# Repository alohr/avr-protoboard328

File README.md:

avr-protoboard328
=================

A prototyping board for the AVR atmega328p. 

## Images

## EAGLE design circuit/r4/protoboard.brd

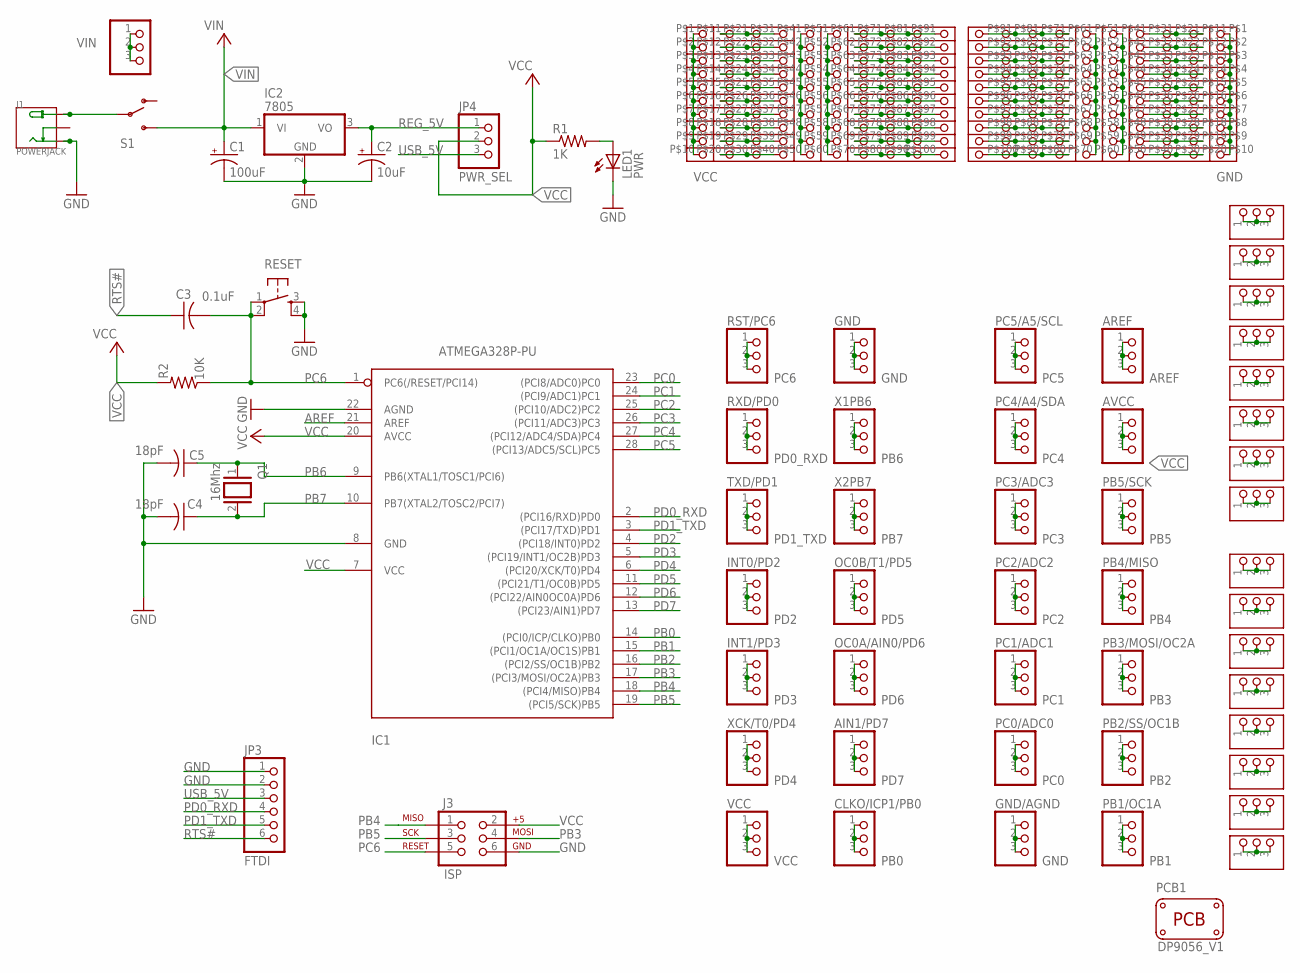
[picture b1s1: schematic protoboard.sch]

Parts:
AIN1/PD7: PINHD-1X3; 1X03
AREF: PINHD-1X3; 1X03
AVCC: PINHD-1X3; 1X03
C1: 100uF; CPOL-RADIAL-100UF-25V
C2: 10uF; CPOL-RADIAL-10UF-25V
C3: 0.1uF; C025-025X050
C4, C5: 18pF; C025-025X050
CLKO/ICP1/PB0: PINHD-1X3; 1X03
GND: PINHD-1X3; 1X03
GND/AGND: PINHD-1X3; 1X03
IC1: ATMEGA328P-PU; DIL28-3
IC2: 7805; TO220H
INT0/PD2, INT1/PD3: PINHD-1X3; 1X03
J1: POWERJACK; PW-3P-2.1
J3: ISP; 2X3
JP3: FTDI; 1X06
JP4: PWR_SEL; 1X03
LED1: PWR; LED3MM
OC0A/AIN0/PD6, OC0B/T1/PD5: PINHD-1X3; 1X03
PB1/OC1A, PB2/SS/OC1B, PB3/MOSI/OC2A, PB4/MISO, PB5/SCK: PINHD-1X3; 1X03
PC0/ADC0, PC1/ADC1, PC2/ADC2, PC3/ADC3, PC4/A4/SDA, PC5/A5/SCL: PINHD-1X3; 1X03
PCB1: PCB_DP_RECTANGLE-56X90; DP9056_V1
Q1: 16Mhz; QS
R1: 1K; 0207/7
R2: 10K; 0207/7
RESET: TAC_SWITCHPTH; TACTILE-PTH
RST/PC6: PINHD-1X3; 1X03
RXD/PD0: PINHD-1X3; 1X03
S1: SWITCH-SPDTPTH; SWITCH-SPDT
TXD/PD1: PINHD-1X3; 1X03
U$1, U$3: PROTOFIELD-10X10
U$4, U$5, U$6, U$7, U$8, U$9, U$10, U$11, U$12, U$13, U$14, U$15, U$16, U$17, U$18, U$19: PROTOFIELD-3
VCC: PINHD-1X3; 1X03
VIN: +9V; 1X03
X1PB6, X2PB7: PINHD-1X3; 1X03
XCK/T0/PD4: PINHD-1X3; 1X03

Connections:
AREF: AREF.1, AREF.2, AREF.3, IC1.21 (AREF)
GND: C1.2 (-), C2.2 (-), C4.2, C5.2, GND.1, GND.2, GND.3, GND/AGND.1, GND/AGND.2, GND/AGND.3, IC1.8 (GND), IC1.22 (AGND), IC2.2 (GND), J1.-1 (-), J3.6, JP3.1, JP3.2, LED1.K (C), RESET.3, RESET.4, U$3.P$1 (1), U$3.P$2 (5), U$3.P$3, U$3.P$4, U$3.P$5, U$3.P$6, U$3.P$7, U$3.P$8, U$3.P$9, U$3.P$10
unnamed: J1.+, S1.2
unnamed: LED1.A, R1.2
unnamed: U$4.1, U$4.2, U$4.3
unnamed: U$5.1, U$5.2, U$5.3
unnamed: U$6.1, U$6.2, U$6.3
unnamed: U$7.1, U$7.2, U$7.3
unnamed: U$8.1, U$8.2, U$8.3
unnamed: U$9.1, U$9.2, U$9.3
unnamed: U$10.1, U$10.2, U$10.3
unnamed: U$11.1, U$11.2, U$11.3
unnamed: U$12.1, U$12.2, U$12.3
unnamed: U$13.1, U$13.2, U$13.3
unnamed: U$14.1, U$14.2, U$14.3
unnamed: U$15.1, U$15.2, U$15.3
unnamed: U$16.1, U$16.2, U$16.3
unnamed: U$17.1, U$17.2, U$17.3
unnamed: U$18.1, U$18.2, U$18.3
unnamed: U$19.1, U$19.2, U$19.3
unnamed: U$1.P$41, U$1.P$42, U$1.P$43, U$1.P$44, U$1.P$45, U$1.P$46, U$1.P$47, U$1.P$48, U$1.P$49, U$1.P$50
unnamed: U$1.P$51, U$1.P$52, U$1.P$53, U$1.P$54, U$1.P$55, U$1.P$56, U$1.P$57, U$1.P$58, U$1.P$59, U$1.P$60
unnamed: U$1.P$61, U$1.P$71, U$1.P$81, U$1.P$91
unnamed: U$1.P$62, U$1.P$72, U$1.P$82, U$1.P$92
unnamed: U$1.P$63, U$1.P$73, U$1.P$83, U$1.P$93
unnamed: U$1.P$64, U$1.P$74, U$1.P$84, U$1.P$94
unnamed: U$1.P$65, U$1.P$75, U$1.P$85, U$1.P$95
unnamed: U$1.P$66, U$1.P$76, U$1.P$86, U$1.P$96
unnamed: U$1.P$67, U$1.P$77, U$1.P$87, U$1.P$97
unnamed: U$1.P$68, U$1.P$78, U$1.P$88, U$1.P$98
unnamed: U$1.P$69, U$1.P$79, U$1.P$89, U$1.P$99
unnamed: U$1.P$70, U$1.P$80, U$1.P$90, U$1.P$100
unnamed: U$1.P$11 (2), U$1.P$21 (3), U$1.P$31 (4)
unnamed: U$1.P$12 (6), U$1.P$22 (7), U$1.P$32 (8)
unnamed: U$1.P$13, U$1.P$23, U$1.P$33
unnamed: U$1.P$14, U$1.P$24, U$1.P$34
unnamed: U$1.P$15, U$1.P$25, U$1.P$35
unnamed: U$1.P$16, U$1.P$26, U$1.P$36
unnamed: U$1.P$17, U$1.P$27, U$1.P$37
unnamed: U$1.P$18, U$1.P$28, U$1.P$38
unnamed: U$1.P$19, U$1.P$29, U$1.P$39
unnamed: U$1.P$20, U$1.P$30, U$1.P$40
unnamed: U$3.P$61, U$3.P$71, U$3.P$81, U$3.P$91
unnamed: U$3.P$62, U$3.P$72, U$3.P$82, U$3.P$92
unnamed: U$3.P$63, U$3.P$73, U$3.P$83, U$3.P$93
unnamed: U$3.P$64, U$3.P$74, U$3.P$84, U$3.P$94
unnamed: U$3.P$65, U$3.P$75, U$3.P$85, U$3.P$95
unnamed: U$3.P$66, U$3.P$76, U$3.P$86, U$3.P$96
unnamed: U$3.P$67, U$3.P$77, U$3.P$87, U$3.P$97
unnamed: U$3.P$68, U$3.P$78, U$3.P$88, U$3.P$98
unnamed: U$3.P$69, U$3.P$79, U$3.P$89, U$3.P$99
unnamed: U$3.P$70, U$3.P$80, U$3.P$90, U$3.P$100
unnamed: U$3.P$51, U$3.P$52, U$3.P$53, U$3.P$54, U$3.P$55, U$3.P$56, U$3.P$57, U$3.P$58, U$3.P$59, U$3.P$60
unnamed: U$3.P$41, U$3.P$42, U$3.P$43, U$3.P$44, U$3.P$45, U$3.P$46, U$3.P$47, U$3.P$48, U$3.P$49, U$3.P$50
unnamed: U$3.P$11 (2), U$3.P$21 (3), U$3.P$31 (4)
unnamed: U$3.P$12 (6), U$3.P$22 (7), U$3.P$32 (8)
unnamed: U$3.P$13, U$3.P$23, U$3.P$33
unnamed: U$3.P$14, U$3.P$24, U$3.P$34
unnamed: U$3.P$15, U$3.P$25, U$3.P$35
unnamed: U$3.P$16, U$3.P$26, U$3.P$36
unnamed: U$3.P$17, U$3.P$27, U$3.P$37
unnamed: U$3.P$18, U$3.P$28, U$3.P$38
unnamed: U$3.P$19, U$3.P$29, U$3.P$39
unnamed: U$3.P$20, U$3.P$30, U$3.P$40
PB0: CLKO/ICP1/PB0.1, CLKO/ICP1/PB0.2, CLKO/ICP1/PB0.3, IC1.14 ((PCI0/ICP/CLKO)PB0)
PB1: IC1.15 ((PCI1/OC1A/OC1S)PB1), PB1/OC1A.1, PB1/OC1A.2, PB1/OC1A.3
PB2: IC1.16 ((PCI2/SS/OC1B)PB2), PB2/SS/OC1B.1, PB2/SS/OC1B.2, PB2/SS/OC1B.3
PB3: IC1.17 ((PCI3/MOSI/OC2A)PB3), J3.4, PB3/MOSI/OC2A.1, PB3/MOSI/OC2A.2, PB3/MOSI/OC2A.3
PB4: IC1.18 ((PCI4/MISO)PB4), J3.1, PB4/MISO.1, PB4/MISO.2, PB4/MISO.3
PB5: IC1.19 ((PCI5/SCK)PB5), J3.3, PB5/SCK.1, PB5/SCK.2, PB5/SCK.3
PB6: C5.1, IC1.9 (PB6(XTAL1/TOSC1/PCI6)), Q1.1, X1PB6.1, X1PB6.2, X1PB6.3
PB7: C4.1, IC1.10 (PB7(XTAL2/TOSC2/PCI7)), Q1.2, X2PB7.1, X2PB7.2, X2PB7.3
PC0: IC1.23 ((PCI8/ADC0)PC0), PC0/ADC0.1, PC0/ADC0.2, PC0/ADC0.3
PC1: IC1.24 ((PCI9/ADC1)PC1), PC1/ADC1.1, PC1/ADC1.2, PC1/ADC1.3
PC2: IC1.25 ((PCI10/ADC2)PC2), PC2/ADC2.1, PC2/ADC2.2, PC2/ADC2.3
PC3: IC1.26 ((PCI11/ADC3)PC3), PC3/ADC3.1, PC3/ADC3.2, PC3/ADC3.3
PC4: IC1.27 ((PCI12/ADC4/SDA)PC4), PC4/A4/SDA.1, PC4/A4/SDA.2, PC4/A4/SDA.3
PC5: IC1.28 ((PCI13/ADC5/SCL)PC5), PC5/A5/SCL.1, PC5/A5/SCL.2, PC5/A5/SCL.3
PC6: C3.2, IC1.1 (PC6(/RESET/PCI14)), J3.5, R2.1, RESET.1, RESET.2, RST/PC6.1, RST/PC6.2, RST/PC6.3
PD0_RXD: IC1.2 ((PCI16/RXD)PD0), JP3.4, RXD/PD0.1, RXD/PD0.2, RXD/PD0.3
PD1_TXD: IC1.3 ((PCI17/TXD)PD1), JP3.5, TXD/PD1.1, TXD/PD1.2, TXD/PD1.3
PD2: IC1.4 ((PCI18/INT0)PD2), INT0/PD2.1, INT0/PD2.2, INT0/PD2.3
PD3: IC1.5 ((PCI19/INT1/OC2B)PD3), INT1/PD3.1, INT1/PD3.2, INT1/PD3.3
PD4: IC1.6 ((PCI20/XCK/T0)PD4), XCK/T0/PD4.1, XCK/T0/PD4.2, XCK/T0/PD4.3
PD5: IC1.11 ((PCI21/T1/OC0B)PD5), OC0B/T1/PD5.1, OC0B/T1/PD5.2, OC0B/T1/PD5.3
PD6: IC1.12 ((PCI22/AIN0OC0A)PD6), OC0A/AIN0/PD6.1, OC0A/AIN0/PD6.2, OC0A/AIN0/PD6.3
PD7: AIN1/PD7.1, AIN1/PD7.2, AIN1/PD7.3, IC1.13 ((PCI23/AIN1)PD7)
REG_5V: C2.1 (+), IC2.3 (VO), JP4.1
RTS#: C3.1, JP3.6
USB_5V: JP3.3, JP4.3
VCC: AVCC.1, AVCC.2, AVCC.3, IC1.7 (VCC), IC1.20 (AVCC), J3.2, JP4.2, R1.1, R2.2, U$1.P$1 (1), U$1.P$2 (5), U$1.P$3, U$1.P$4, U$1.P$5, U$1.P$6, U$1.P$7, U$1.P$8, U$1.P$9, U$1.P$10, VCC.1, VCC.2, VCC.3
VIN: C1.1 (+), IC2.1 (VI), S1.3 (S), VIN.1, VIN.2, VIN.3

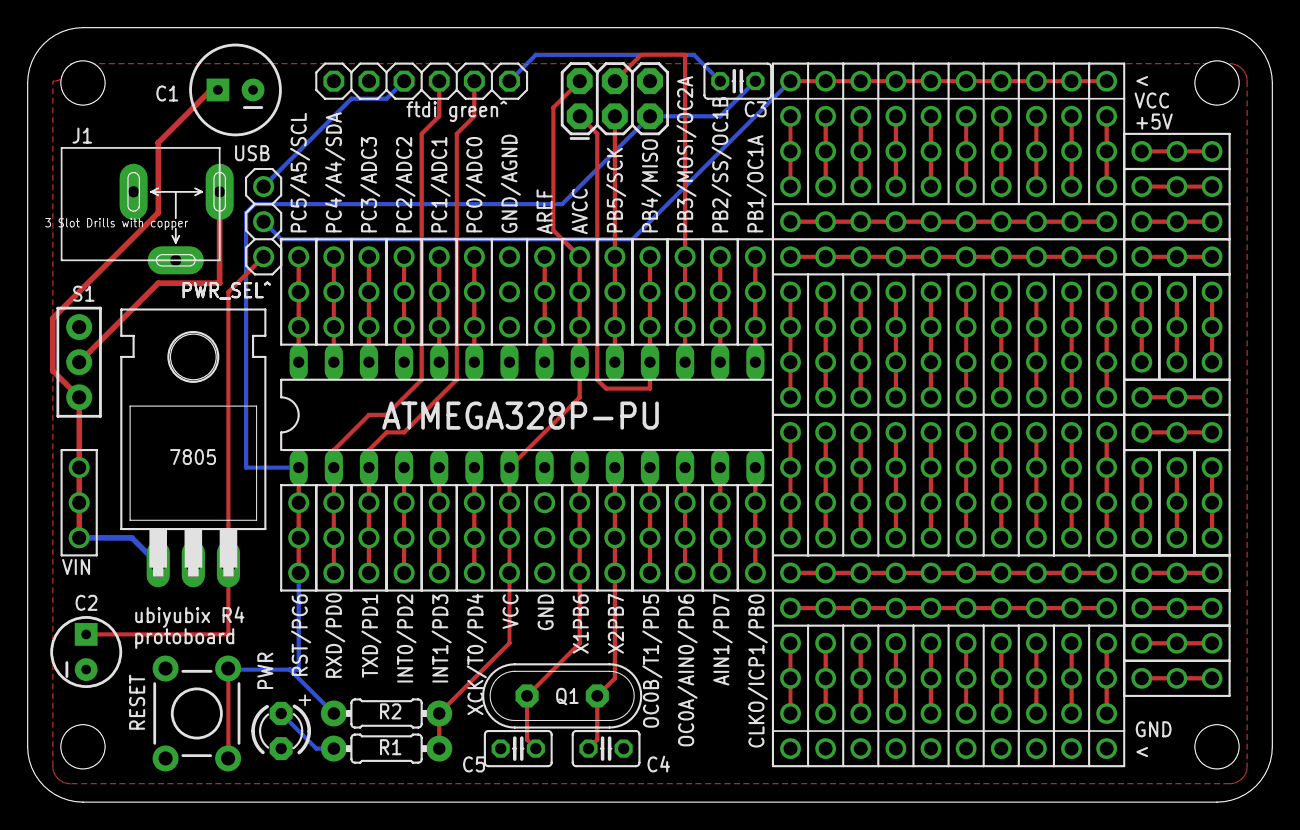
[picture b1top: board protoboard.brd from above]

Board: 2 copper layers, 89.9 x 55.9 mm, 65 parts (0 on the bottom side), 92 nets.

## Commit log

2015-05-25 added image
2015-05-25 link to image
2015-05-25 link to small image
2015-05-25 more images
2015-09-06 added images and examples dir
2015-09-06 images are now in subdir
2015-09-06 removed old files
2015-09-06 added r3 eagle and gerber files
2015-09-06 added serialecho
2015-09-06 renamed blink/main.c -> blink/blink.c
2015-09-06 images location
2016-01-28 fixed attiny85 8 mhz
2016-01-28 renamed main.c -> blink.c
2016-01-28 added examples
2016-02-07 use sendhexword
2016-02-07 removed serial code
2016-02-07 finished
2016-02-14 added pin usage
2016-02-17 reverse direction of potentiometer
2016-02-17 use timer2 for display
2016-02-18 added delaymachine
2017-02-25 added r4
2017-02-25 added seeed files

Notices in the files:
parts and their libraries:
SparkFun-Connectors: Licensing: CC v3.0 Share-Alike You are welcome to use this library for commercial purposes.
